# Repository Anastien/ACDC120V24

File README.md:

A generic 120 W, 24 V ac/dc power supply.

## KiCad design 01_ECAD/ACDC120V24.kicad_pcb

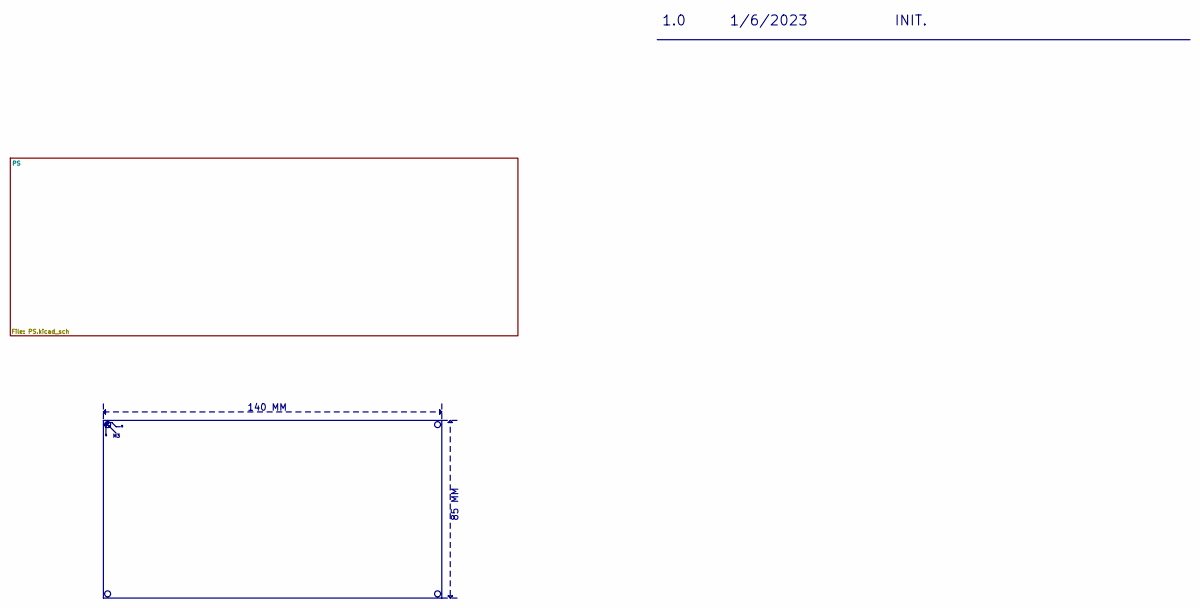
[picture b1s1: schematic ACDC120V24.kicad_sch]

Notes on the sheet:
85 MM
1/6/2023
140 MM
1.0
INIT.

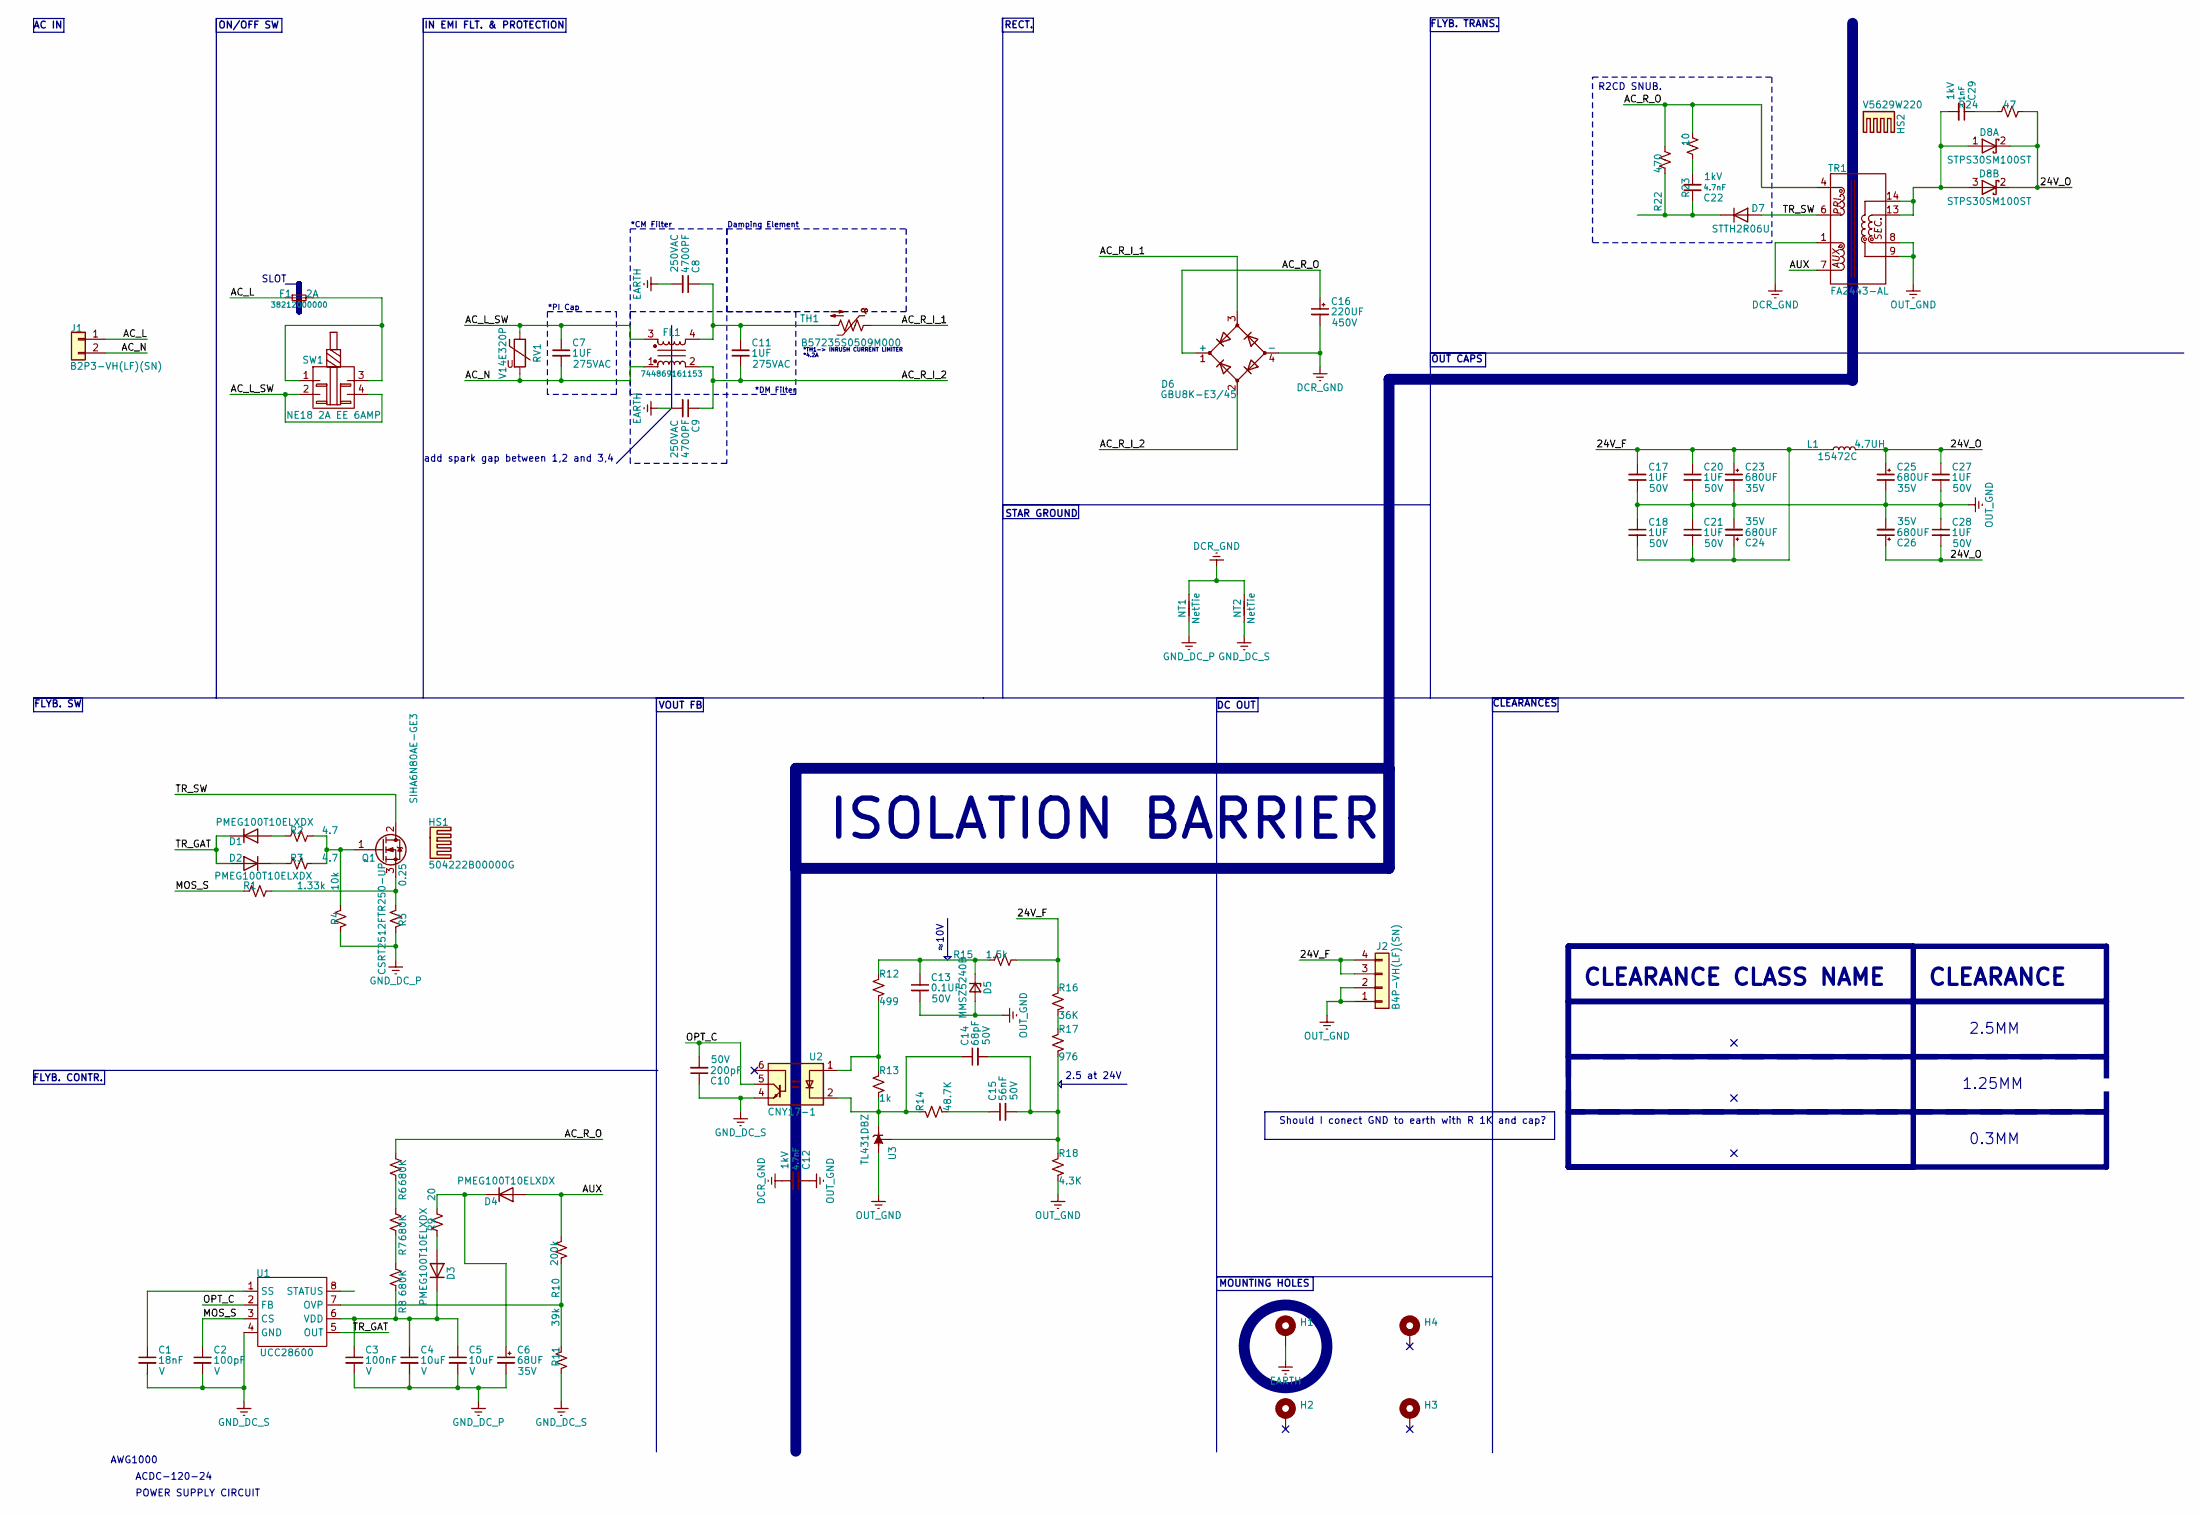
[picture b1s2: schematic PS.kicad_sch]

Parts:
C1: 18nF; C_0603_1608Metric; VOLTAGE V
C2: 100pF; C_0603_1608Metric; VOLTAGE V
C3: 100nF; C_0603_1608Metric; VOLTAGE V
C4, C5: 10uF; C_0603_1608Metric; VOLTAGE V
C6: 68UF; C_Radial_D6.3mm_H11.0mm_P2.50mm; VOLTAGE 35V
C7, C11: 1UF; 890324026027CS; VOLTAGE 275VAC
C8, C9: 4700PF; C_Disc_D10.5mm_W5.0mm_P5.00mm; VOLTAGE 250VAC
C10: 200pF; C_0603_1608Metric; VOLTAGE 50V
C12, C22: 4.7nF; C_Disc_D7.5mm_W5.0mm_P7.50mm; VOLTAGE 1kV
C13: 0.1UF; C_0603_1608Metric; VOLTAGE 50V
C14: 68pF; C_0603_1608Metric; VOLTAGE 50V
C15: 56nF; C_0603_1608Metric; VOLTAGE 50V
C16: 220UF; CP_Radial_D18.0mm_P7.50mm; VOLTAGE 450V
C17, C18, C20, C21, C27, C28: 1UF; C_0805_2012Metric_Pad1.18x1.45mm_HandSolder; VOLTAGE 50V
C23, C24, C25, C26: 680UF; EKZN630ELL681MK30S; VOLTAGE 35V
C29: 1nF; C_Disc_D7.5mm_W5.0mm_P7.50mm; VOLTAGE 1kV
D1, D2, D3, D4: PMEG100T10ELXDX; D_SOD-323
D5: MMSZ5240B; D_SOD-123F
D6: GBU8K-E3/45; Diode_Bridge_Vishay_GBU
D7: STTH2R06U; D_SMB
D8: STPS30SM100ST; TO-220-3_Vertical
F1: 38212000000; 38211000410; Current Rating 2A
FL1: 744869161153
H1, H2, H3, H4: MountingHole_Pad; MountingHole_3.2mm_M3_DIN965_Pad_TopBottom
HS1: 504222B00000G
HS2: V5629W220
J1: B2P3-VH(LF)(SN); JST_VH_B2P3-VH_1x02_P7.92mm_Vertical
J2: B4P-VH(LF)(SN); JST_VH_B4P-VH-B_1x04_P3.96mm_Vertical
L1: 4.7UH; 744750340047
NT1: NetTie; NetTie-2_SMD_Pad2.0mm
NT2: NetTie; NetTie-2_SMD_Pad0.5mm
Q1: SIHA6N80AE-GE3
R1: 1.33k; R_0603_1608Metric
R2, R3: 4.7; R_0603_1608Metric
R4: 10k; R_0603_1608Metric
R5: 0.25; R_2512_6332Metric_Pad1.40x3.35mm_HandSolder
R6, R7, R8: 680K; R_1206_3216Metric_Pad1.30x1.75mm_HandSolder
R9: 20; R_0603_1608Metric
R10: 200k; R_0603_1608Metric
R11: 39k; R_0603_1608Metric
R12: 499; R_0603_1608Metric
R13: 1k; R_0603_1608Metric
R14: 48.7K; R_0603_1608Metric
R15: 1.5k; R_0603_1608Metric
R16: 36K; R_0603_1608Metric
R17: 976; R_0603_1608Metric
R18: 4.3K; R_0603_1608Metric
R22: 470; R_Axial_DIN0516_L15.5mm_D5.0mm_P5.08mm_Vertical
R23: 10; R_Axial_DIN0516_L15.5mm_D5.0mm_P5.08mm_Vertical
R24: 47; R_Axial_DIN0516_L15.5mm_D5.0mm_P5.08mm_Vertical
RV1: V14E320P; RV_Disc_D16.5mm_W6.7mm_P7.5mm
SW1: NE18 2A EE 6AMP; NE1846EE
TH1: B57235S0509M000; RV_Disc_D9mm_W6.1mm_P5mm
TR1: FA2443-AL
U1: UCC28600; SOIC-8_3.9x4.9mm_P1.27mm
U2: CNY17-1; DIP-6_W7.62mm_LongPads
U3: TL431DBZ; SOT-23

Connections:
/PS/24V_F: C17.1, C18.2, C20.1, C21.2, C23.1, C24.1, J2.3, J2.4, L1.1, R15.2, R16.2
/PS/24V_O: C25.1, C26.1, C27.1, C28.2, D8.2 (K), L1.2, R24.2
/PS/AC_L: F1.1, J1.1
/PS/AC_L_SW: C7.1, FL1.3, RV1.1, SW1.2, SW1.4
/PS/AC_N: C7.2, FL1.1, J1.2, RV1.2
/PS/AC_R_I_1: D6.3, TH1.1
/PS/AC_R_I_2: C9.1, C11.2, D6.2, FL1.2
/PS/AC_R_O: C16.1, D6.1 (+), R6.2, R22.2, R23.2, TR1.4
/PS/AUX: D4.2 (A), R10.2, TR1.7
/PS/MOS_S: C2.1, R1.2, U1.3 (CS)
/PS/OPT_C: C10.2, U1.2 (FB), U2.5
/PS/TR_GAT: D1.1 (K), D2.2 (A), U1.5 (OUT)
/PS/TR_SW: D7.2 (A), Q1.2 (D), TR1.6
DCR_GND: C12.2, C16.2, D6.4 (-), NT1.2, NT2.2, TR1.1
EARTH: C8.2, C9.2, H1.1
GND_DC_P: C3.2, C4.2, C5.2, C6.2, NT1.1, R4.2, R5.2
GND_DC_S: C1.2, C2.2, C10.1, NT2.1, R11.2, U1.4 (GND), U2.4
unnamed: C8.1, C11.1, FL1.4, TH1.2
unnamed: C15.1, R14.1
unnamed: C22.2, R23.1
unnamed: C29.1, R24.1
unnamed: D1.2 (A), R2.2
unnamed: D2.1 (K), R3.2
unnamed: D3.2 (A), R9.2
unnamed: C3.1, C4.1, C5.1, D3.1 (K), R8.1, U1.6 (VDD)
unnamed: C6.1, D4.1 (K), R9.1
unnamed: C13.1, D5.1 (K), R12.2, R15.1
unnamed: C22.1, D7.1 (K), R22.1
unnamed: C29.2, D8.1 (A), D8.3 (K), TR1.13, TR1.14
unnamed: F1.2, SW1.1, SW1.3
unnamed: Q1.1 (G), R2.1, R3.1, R4.1
unnamed: Q1.3 (S), R1.1, R5.1
unnamed: R6.1, R7.2
unnamed: R7.1, R8.2
unnamed: R12.1, R13.2, U2.1
unnamed: R16.1, R17.2
unnamed: R10.1, R11.1, U1.7 (OVP)
unnamed: C1.1, U1.1 (SS)
unnamed: C14.1, R13.1, R14.2, U2.2, U3.1 (K)
unnamed: C14.2, C15.2, R17.1, R18.2, U3.2 (REF)
OUT_GND: C12.1, C13.2, C17.2, C18.1, C20.2, C21.1, C23.2, C24.2, C25.2, C26.2, C27.2, C28.1, D5.2 (A), J2.1, J2.2, R18.1, TR1.8, TR1.9, U3.3 (A)

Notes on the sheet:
CLEARANCE CLASS NAME
MOUNTING HOLES
2.5MM
OUT CAPS
RECT.
VOUT FB
POWER SUPPLY CIRCUIT
IN EMI FLT. & PROTECTION
AC IN
1.25MM
CLEARANCE
2.5 at 24V
*PI Cap
Damping Element
add spark gap between 1,2 and 3,4
FLYB. CONTR.
*4.2A
CLEARANCES
≈10V
AWG1000
*CM Filter
Should I conect GND to earth with R 1K and cap?
FLYB. TRANS.
ACDC-120-24
*DM Filter
*TH1-> INRUSH CURRENT LIMITER
DC OUT
STAR GROUND
ON/OFF SW
ISOLATION BARRIER
0.3MM
FLYB. SW
SLOT
R2CD SNUB.

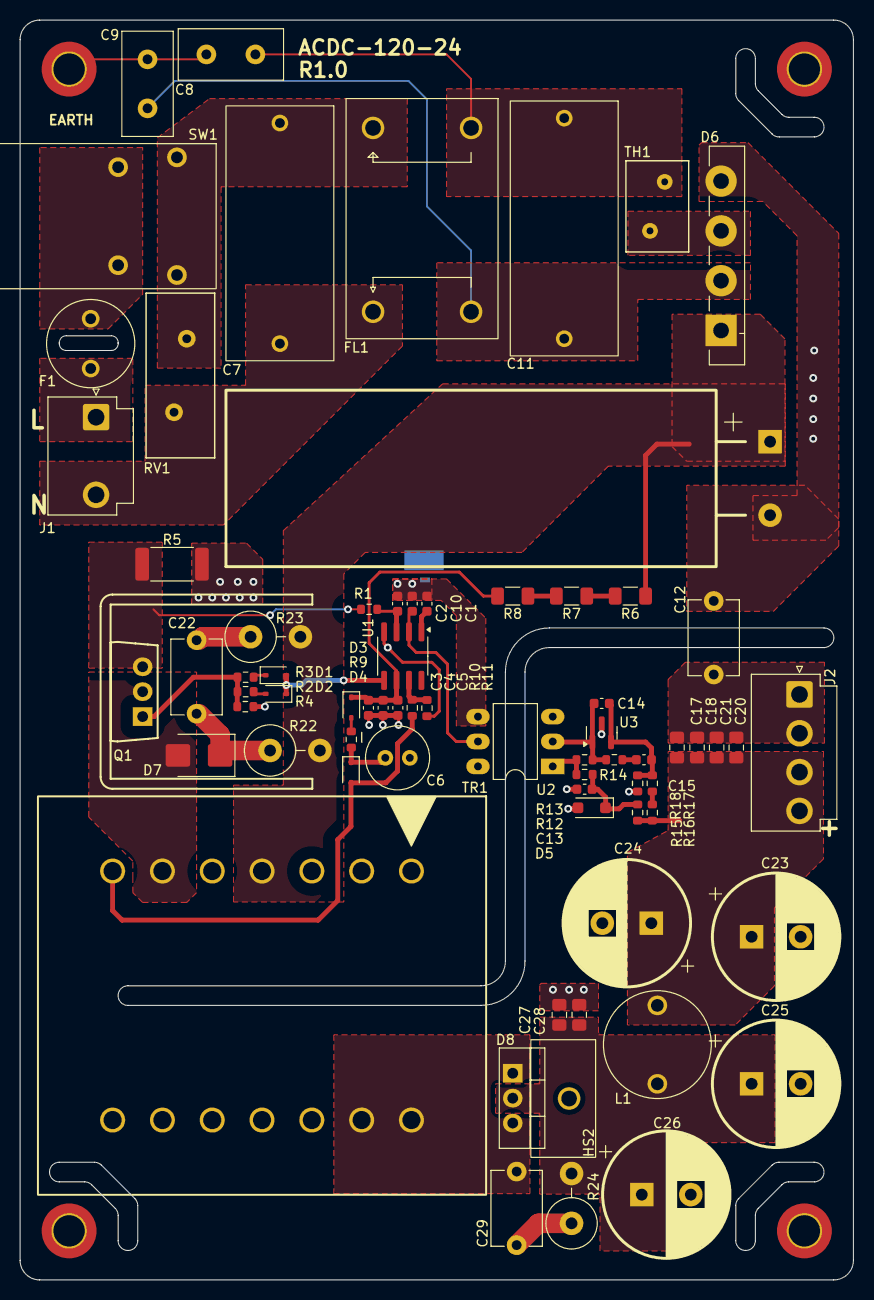
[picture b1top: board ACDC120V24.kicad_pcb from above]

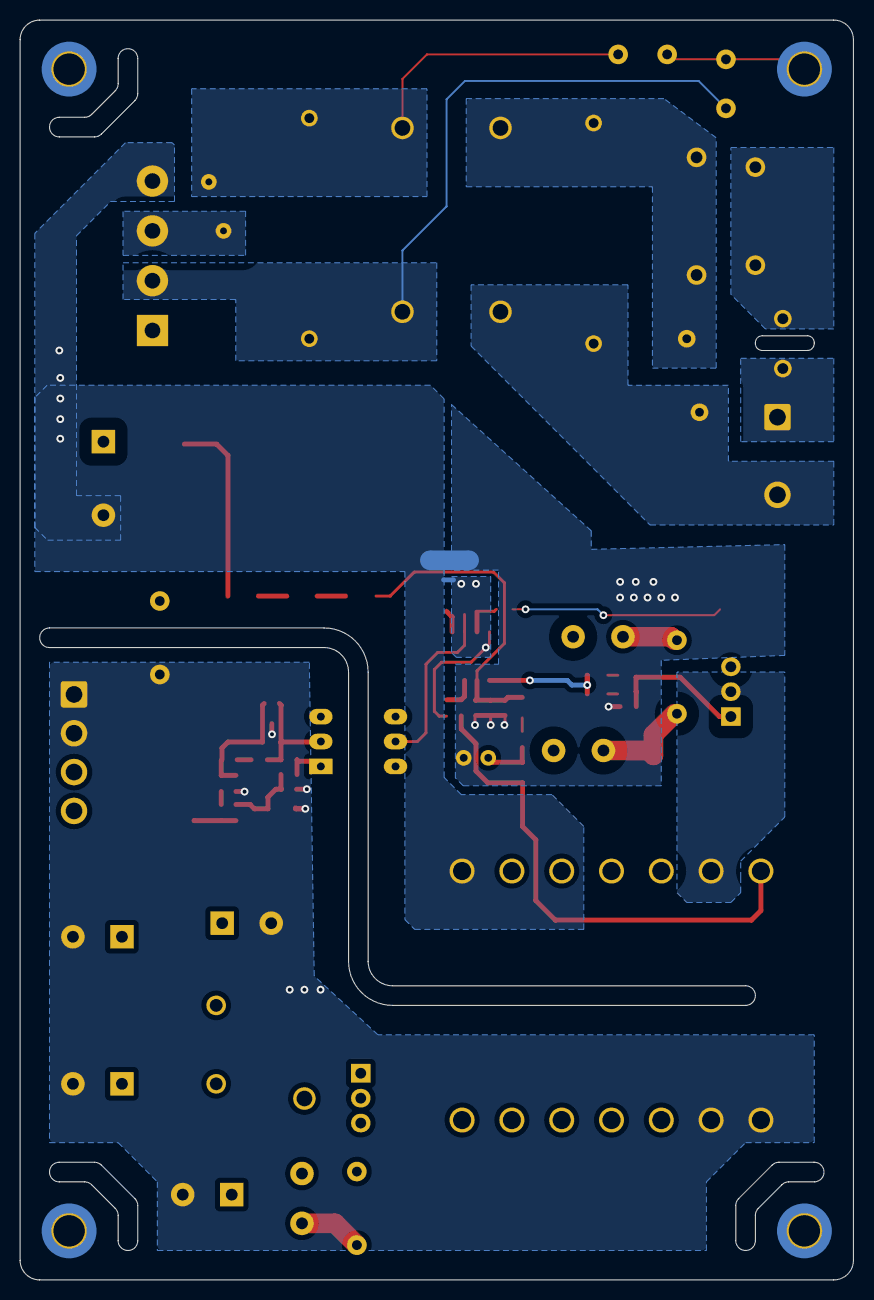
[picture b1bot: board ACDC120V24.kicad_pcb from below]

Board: 2 copper layers, 85.0 x 128.5 mm, 77 parts (3 on the bottom side), 41 nets.

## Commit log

2023-08-30 INIT.
2023-09-03 *Adding Feedback Circuit Simulation.
2023-09-04 Update.
2023-09-13 FOLDER STRUCTURE UPDATE.
2023-09-17 UPDATE!
2023-11-21 Adding To-Do.txt , First initial working Design.
2023-12-09 Regular Update.
2024-02-17 Changing Mosfet.
2024-05-20 Update from 150W to 120W.
